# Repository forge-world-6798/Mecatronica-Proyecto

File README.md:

# Mecatronica-Proyecto

All the documentation and data is in the [wiki](https://github.com/forge-world-6798/Mecatronica-Proyecto/wiki).

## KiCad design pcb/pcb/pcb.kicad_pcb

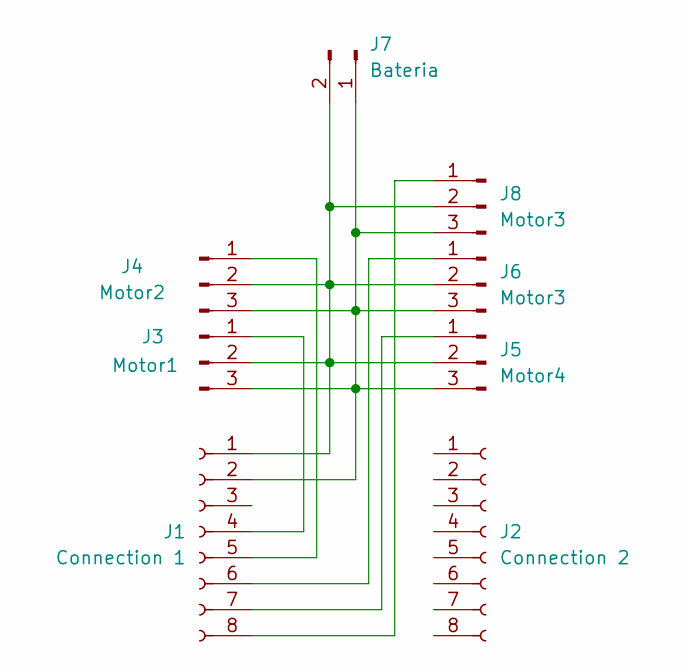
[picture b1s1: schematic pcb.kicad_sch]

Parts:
J1: Connection 1; PinSocket_1x08_P2.54mm_Vertical
J2: Connection 2; PinSocket_1x08_P2.54mm_Vertical
J3: Motor1; PinHeader_1x03_P2.54mm_Vertical
J4: Motor2; PinHeader_1x03_P2.54mm_Vertical
J5: Motor4; PinHeader_1x03_P2.54mm_Vertical
J6, J8: Motor3; PinHeader_1x03_P2.54mm_Vertical
J7: Bateria; PinHeader_1x02_P2.54mm_Vertical

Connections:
unnamed: J1.1, J3.2, J4.2, J5.2, J6.2, J7.2, J8.2
unnamed: J1.2, J3.3, J4.3, J5.3, J6.3, J7.1, J8.3
unnamed: J1.4, J3.1
unnamed: J1.5, J4.1
unnamed: J1.6, J6.1
unnamed: J1.7, J5.1
unnamed: J1.8, J8.1

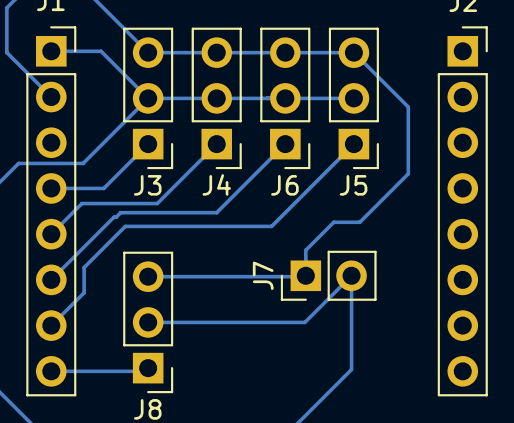
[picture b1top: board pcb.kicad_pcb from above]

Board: 2 copper layers, 8 parts (0 on the bottom side), 7 nets.

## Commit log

2024-09-11 Update issue templates
2024-09-11 Add pull template
2024-09-11 Added Dreadnought STLs
2024-09-11 Added files for a walker that uses very little plastic
2024-09-16 Dodged a lawsuit
2024-10-23 Add 3d
2024-11-04 Add video
2024-11-18 Upload some tests
2024-11-18 readme update
2024-11-23 Add more testing
2024-11-23 Adding camera dev videos
2024-11-24 Missing actions
2024-11-24 More videos
2024-11-25 Adding theme and actions
2024-11-25 Add pcb files
2024-12-01 End software development
2024-12-01 Go bWD
2024-12-01 Change rot directions
2024-12-01 Add hand made movement
2024-12-01 Final software
2024-12-02 Change wifi settings
2024-12-02 Update pcb
2024-12-05 Update pcb and videos
2024-12-05 Moving svgs
2024-12-05 Add colored svgs
2024-12-05 Reduce size of video
2024-12-08 parts designed in freecad format
2024-12-09 Add img and gifs
2024-12-11 Add gerber files
2025-01-02 updated blueprints
2025-01-07 Assembly of the robot
    File with all the parts and an assembly of the robot
2025-01-07 Assmbly + image
    File with all the parts and an assembly of the robot
